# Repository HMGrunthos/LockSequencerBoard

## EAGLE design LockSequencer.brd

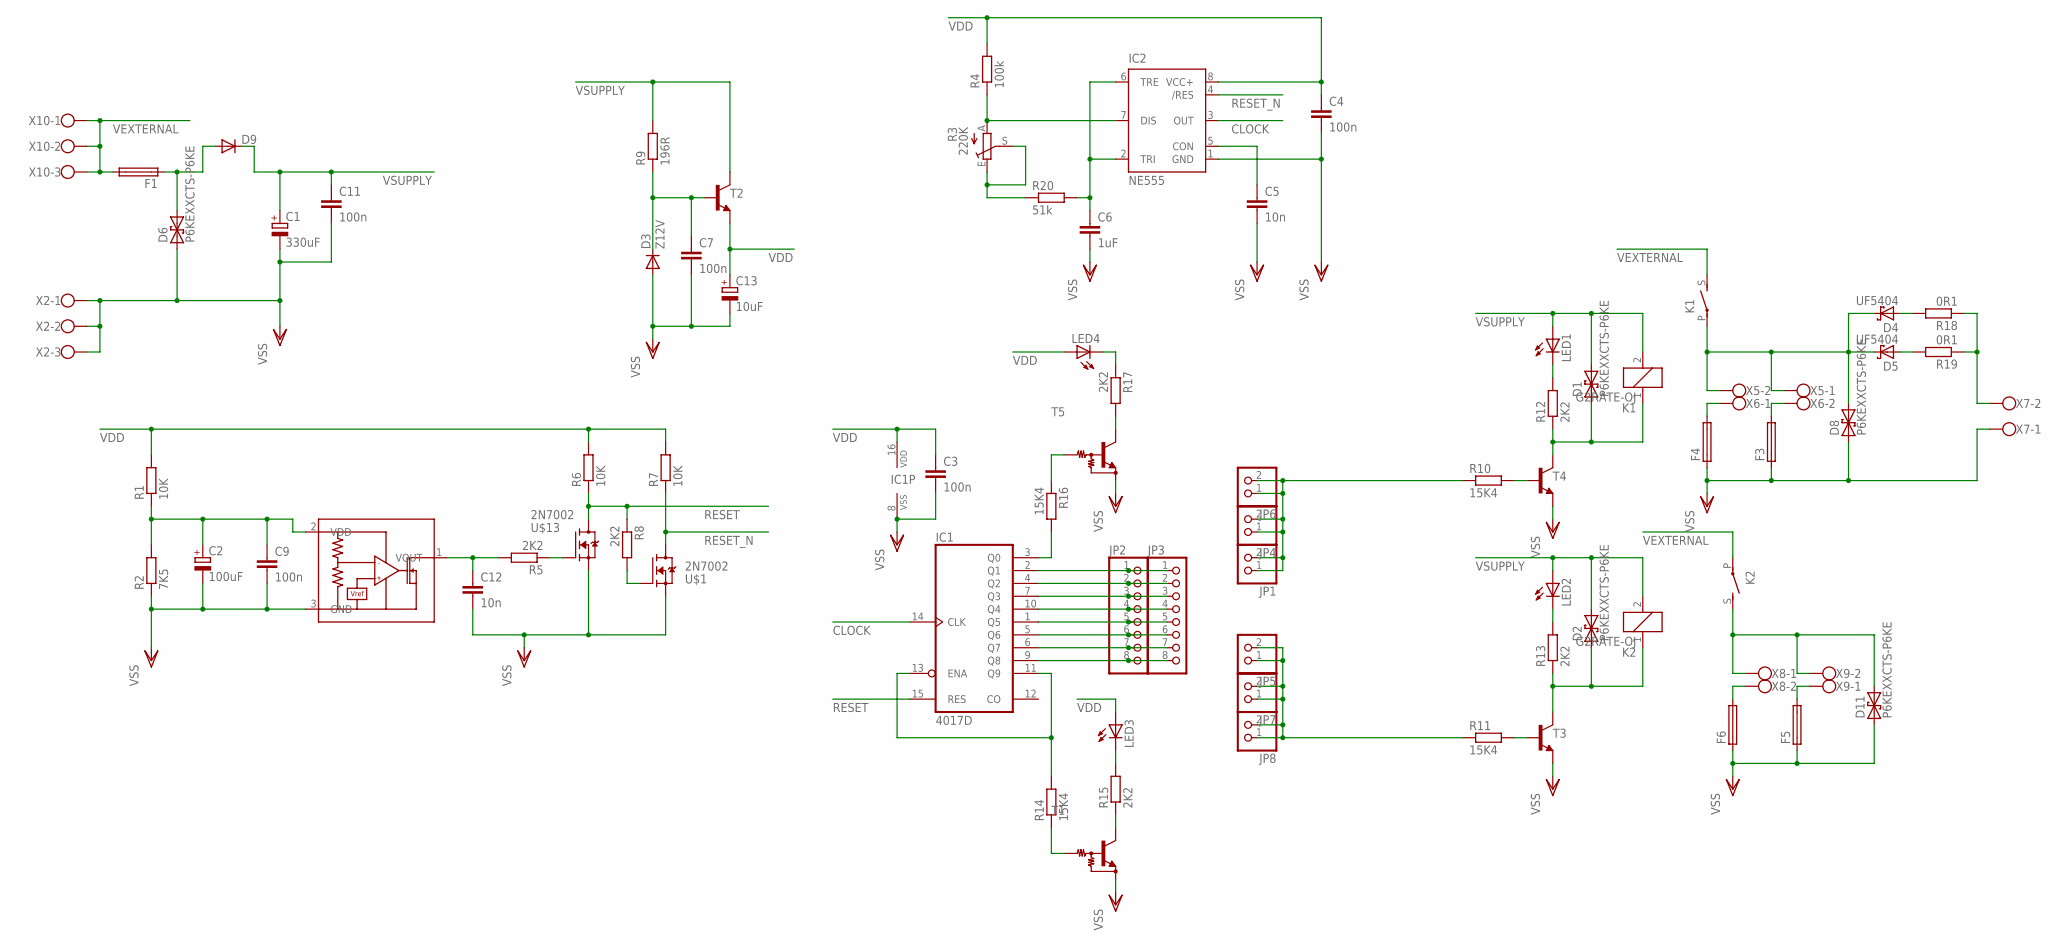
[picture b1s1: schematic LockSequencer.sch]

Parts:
C1: 330uF; E3,5-8
C2: 100uF; E2-5
C3, C7, C9: 100n; C1206K
C4, C11: 100n; C050-024X044
C5, C12: 10n; C1206K
C6: 1uF; C1206K
C13: 10uF; E2-5
D1, D2, D6, D8, D11: P6KEXXCTS-P6KE; DO15-10
D3: Z12V; SOD323-W
D4: UF5404; CB429-15R
D5: UF5404; CB429-15V
D9: DIODE-SOD123; SOD123
F1, F3, F4, F5, F6: TE5
IC1: 4017D; SO16
IC2: NE555; DIL-08
JP1, JP4, JP5, JP6, JP7, JP8: PINHD-1X2; 1X02
JP2, JP3: PINHD-1X8; 1X08
K1, K2: G2RATE-OJ; G2RA-SHORTER
LED1, LED2, LED3, LED4: LED5MM
R1, R6: 10K; 0207/7
R2: 7K5; 0207/7
R3: 220K; CA9V
R4: 100k; 0207/7
R5: 2K2; R0402
R7: 10K; R0805
R8, R12, R13, R15, R17: 2K2; 0207/7
R9: 196R; R0805
R10, R11, R14, R16: 15K4; R0603
R18, R19: 0R1; R2512
R20: 51k; 0207/7
T1, T5: -NPN_DRIVER-; SOT23
T2, T3, T4: MMBTA42LT1-NPN-SOT23-BEC; SOT23-BEC
U$1, U$13: 2N7002; SOT23
U$4: BU48XXG; SOT95P280X125-5N
X2, X10: W237-103
X5, X6, X7, X8, X9: W237-102

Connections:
CLOCK: IC1.14 (CLK), IC2.3 (OUT)
LATCH: JP1.1, JP1.2, JP4.1, JP4.2, JP6.1, JP6.2, R10.1
unnamed: C5.1, IC2.5 (CON)
unnamed: C2.+, C9.1, R1.1, R2.2, U$4.2 (VDD)
unnamed: C12.1, R5.2, U$4.1 (VOUT)
unnamed: IC1.11 (Q9), IC1.13 (ENA), R14.2
unnamed: IC1.5 (Q6), JP2.6, JP3.6
unnamed: IC1.6 (Q7), JP2.7, JP3.7
unnamed: IC1.7 (Q3), JP2.3, JP3.3
unnamed: LED2.K (C), R13.2
unnamed: IC1.1 (Q5), JP2.5, JP3.5
unnamed: LED1.K (C), R12.2
unnamed: F3.2, X6.2
unnamed: IC1.9 (Q8), JP2.8, JP3.8
unnamed: LED4.K (C), R17.1
unnamed: C6.1, IC2.2 (TRI), IC2.6 (TRE), R20.2
unnamed: R10.2, T4.B
unnamed: R14.1, T1.1 (B)
unnamed: R17.2, T5.3 (C)
unnamed: D2.A (1), K2.1, R13.1, T3.C
unnamed: IC1.3 (Q0), R16.2
unnamed: D4.C, D5.C, D8.C (2), K1.P, X5.1, X5.2
unnamed: F5.2, X9.1
unnamed: R5.1, U$13.1 (G)
unnamed: IC2.7 (DIS), R3.A, R4.1
unnamed: C7.1, D3.C, R9.1, T2.B
unnamed: R11.2, T3.B
unnamed: D1.A (1), K1.1, R12.1, T4.C
unnamed: R8.2, U$1.1 (G)
unnamed: D4.A, R18.2
unnamed: F4.2, X6.1
unnamed: R3.E, R3.S, R20.1
unnamed: LED3.K (C), R15.2
unnamed: R15.1, T1.3 (C)
unnamed: IC1.2 (Q1), JP2.1, JP3.1
unnamed: IC1.4 (Q2), JP2.2, JP3.2
unnamed: R16.1, T5.1 (B)
unnamed: D5.A, R19.2
unnamed: IC1.10 (Q4), JP2.4, JP3.4
unnamed: R18.1, R19.1, X7.2
unnamed: D11.C (2), K2.S, X8.1, X9.2
unnamed: F6.2, X8.2
OPEN: JP5.1, JP5.2, JP7.1, JP7.2, JP8.1, JP8.2, R11.1
RESET: IC1.15 (RES), R6.1, R8.1, U$13.3 (D)
RESET_N: IC2.4 (/RES), R7.1, U$1.3 (D)
VDD: C3.1, C4.1, C13.+, IC1.16 (VDD), IC2.8 (VCC+), LED3.A, LED4.A, R1.2, R4.2, R6.2, R7.2, T2.E
VEXTERNAL: F1.2, K1.S, K2.P, X10.1, X10.2, X10.3
VEXTERNAL-FUSED: D6.C (2), D9.A, F1.1
VSS: C1.-, C2.-, C3.2, C4.2, C5.2, C6.2, C7.2, C9.2, C11.2, C12.2, C13.-, D3.A, D6.A (1), D8.A (1), D11.A (1), F3.1, F4.1, F5.1, F6.1, IC1.8 (VSS), IC2.1 (GND), R2.1, T1.2 (E), T3.E, T4.E, T5.2 (E), U$1.2 (S), U$4.3 (GND), U$13.2 (S), X2.1, X2.2, X2.3, X7.1
VSUPPLY: C1.+, C11.1, D1.C (2), D2.C (2), D9.C, K1.2, K2.2, LED1.A, LED2.A, R9.2, T2.C

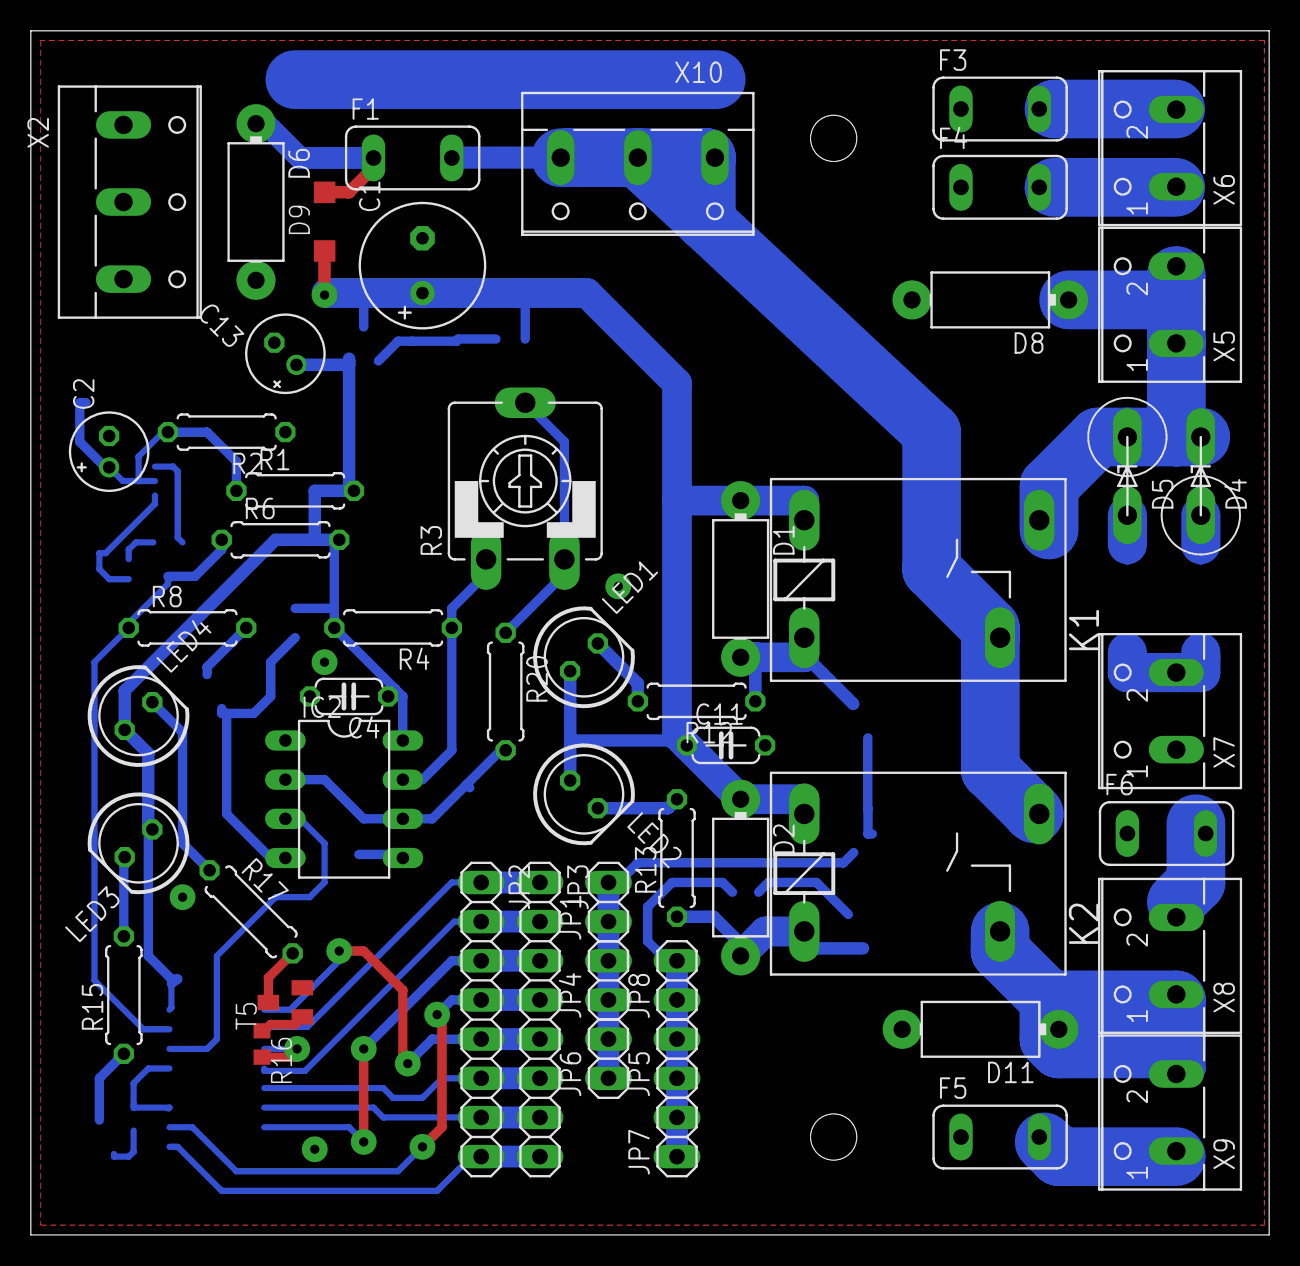
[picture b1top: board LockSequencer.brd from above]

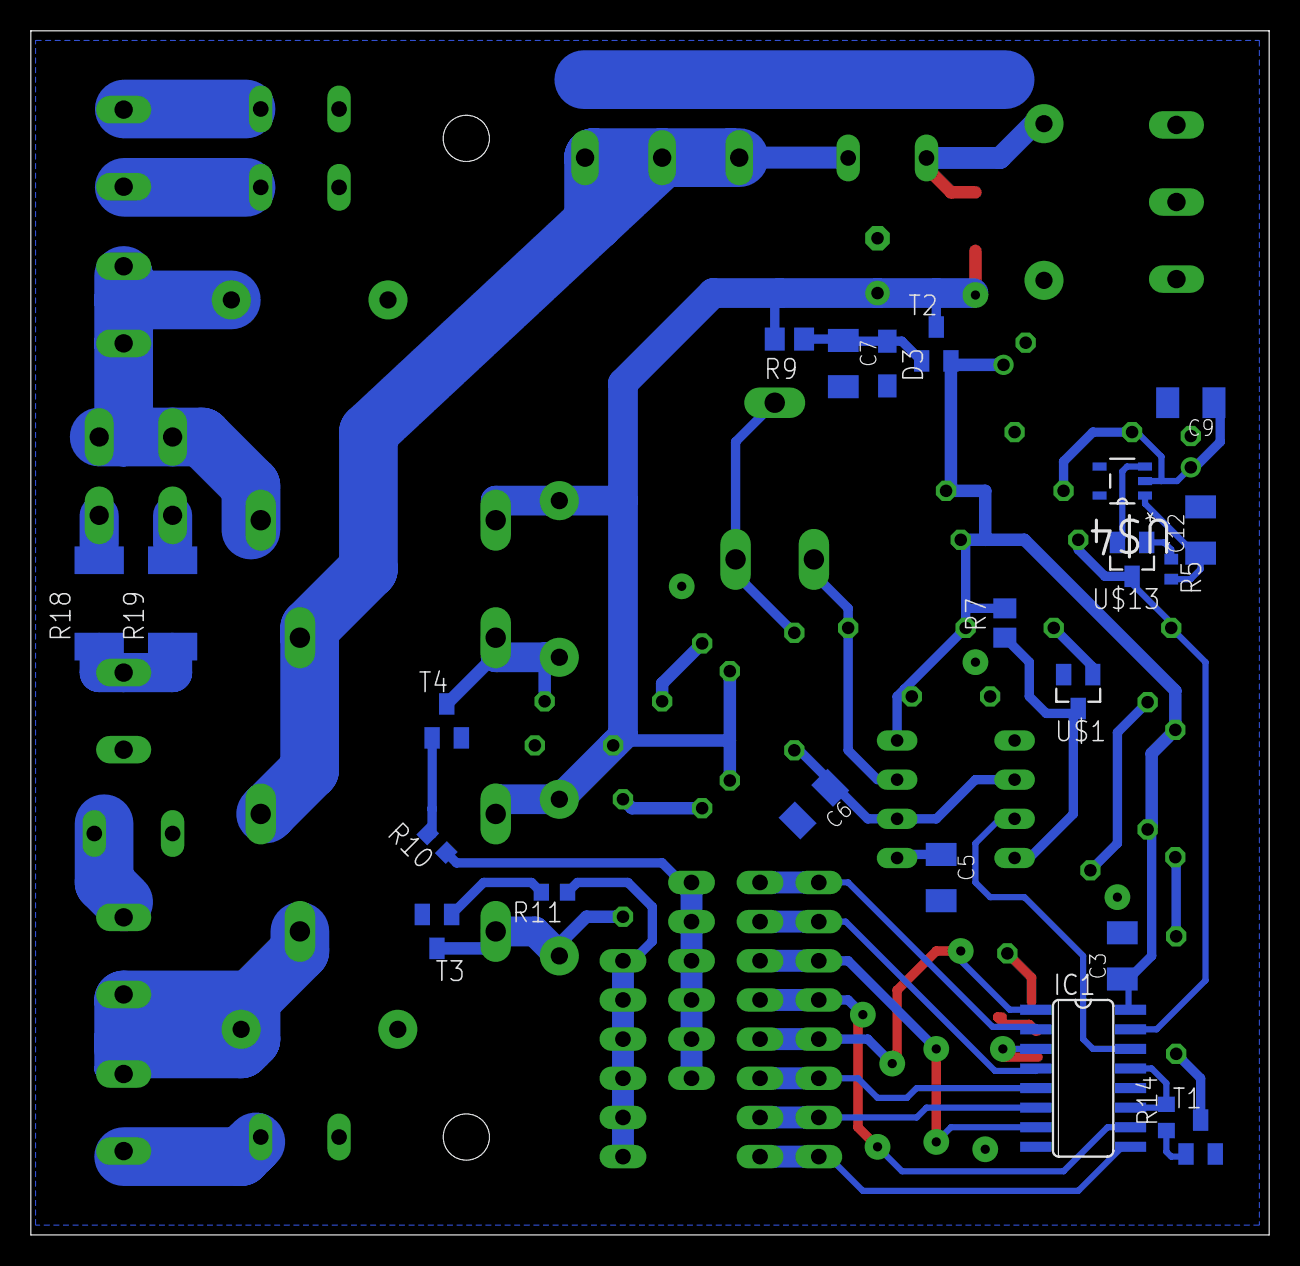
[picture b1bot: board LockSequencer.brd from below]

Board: 2 copper layers, 80.3 x 78.1 mm, 76 parts (23 on the bottom side), 50 nets.

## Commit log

2018-05-17 Initial check in
2018-05-19 Complete versions of the SPICE and Eagle schmatic
2018-05-19 Initial Component placement, removed current sinking to detect polarity
2018-05-19 Initial component placement prior to first auto routing attempt
2018-05-19 Tweaked positions
2018-05-19 555 and 4017 nearly sorted out
2018-05-20 Routing completed
2018-05-20 Final tweaks to layout
2018-05-20 Version at first printout
2018-05-21 Nearly completed second revision
2018-05-22 Nearly finished on second revision - ground and power resrouted on right side of board. 4017 and 55 nearly done.
2018-05-23 Finished relayout ot RHS
2018-05-23 Second revision complete minus DRC
2018-05-23 Completed tweaks to second revision including new package for 1N5819. Ready for printing.
2018-05-24 Added generated PDFs of artwork. Updated BOM and simulation netlist
2018-05-30 Extra revision following minor assembly problems
2018-07-01 Added missing libraries
